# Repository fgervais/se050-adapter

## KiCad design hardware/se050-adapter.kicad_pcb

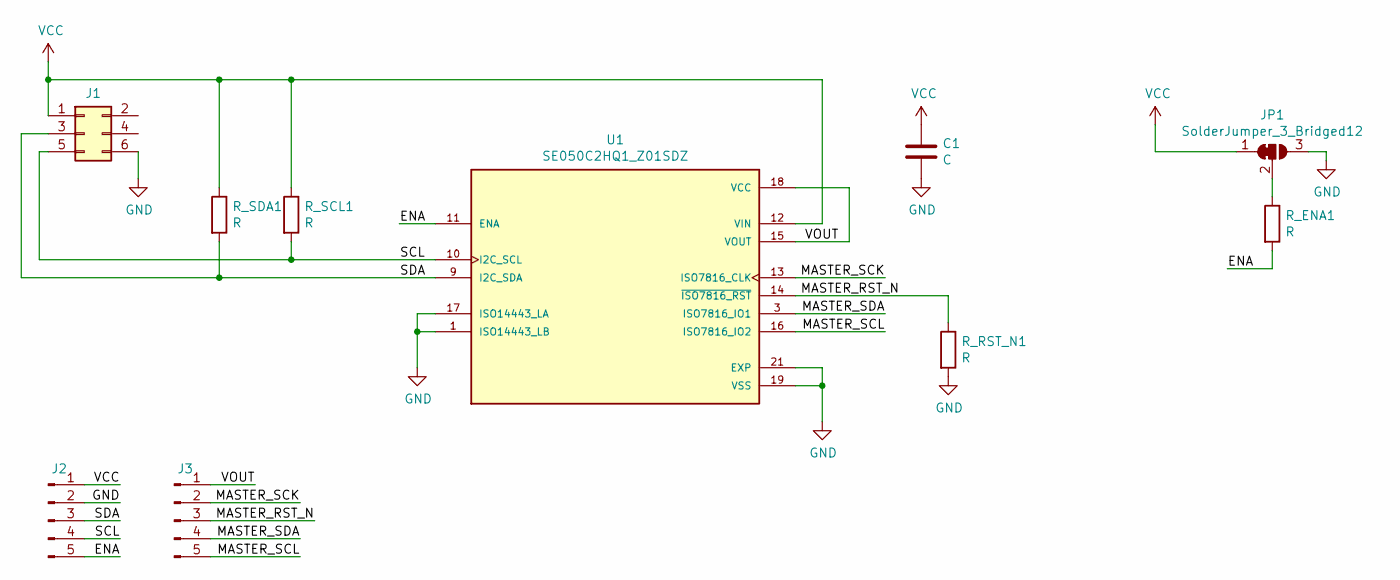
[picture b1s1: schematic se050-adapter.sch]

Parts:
C1: C; R_0603_1608Metric
J1: Conn_02x03_Odd_Even; PinSocket_2x03_P2.54mm_Vertical
J2, J3: Conn_01x05_Male; PinHeader_1x05_P2.54mm_Vertical
JP1: SolderJumper_3_Bridged12; SolderJumper-3_P1.3mm_Bridged12_RoundedPad1.0x1.5mm
R_ENA1: R; R_0603_1608Metric
R_RST_N1: R; R_0603_1608Metric
R_SCL1: R; R_0603_1608Metric
R_SDA1: R; R_0603_1608Metric
U1: SE050C2HQ1_Z01SDZ; QFN40P300X300X33-21N; PARTREV 1.3

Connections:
/ENA: J2.5, R_ENA1.2, U1.11 (ENA)
/MASTER_RST_N: J3.3, R_RST_N1.1, U1.14 (~ISO7816_RST)
/MASTER_SCK: J3.2, U1.13 (ISO7816_CLK)
/MASTER_SCL: J3.5, U1.16 (ISO7816_IO2)
/MASTER_SDA: J3.4, U1.3 (ISO7816_IO1)
/SCL: J1.5, J2.4, R_SCL1.2, U1.10 (I2C_SCL)
/SDA: J1.3, J2.3, R_SDA1.2, U1.9 (I2C_SDA)
/VOUT: J3.1, U1.15 (VOUT), U1.18 (VCC)
GND: C1.2, J1.6, J2.2, JP1.3 (B), R_RST_N1.2, U1.1 (ISO14443_LB), U1.17 (ISO14443_LA), U1.19 (VSS), U1.21 (EXP)
unnamed: JP1.2 (C), R_ENA1.1
VCC: C1.1, J1.1, J2.1, JP1.1 (A), R_SCL1.1, R_SDA1.1, U1.12 (VIN)

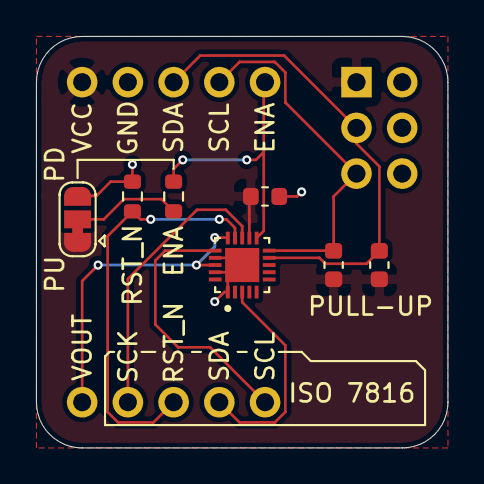
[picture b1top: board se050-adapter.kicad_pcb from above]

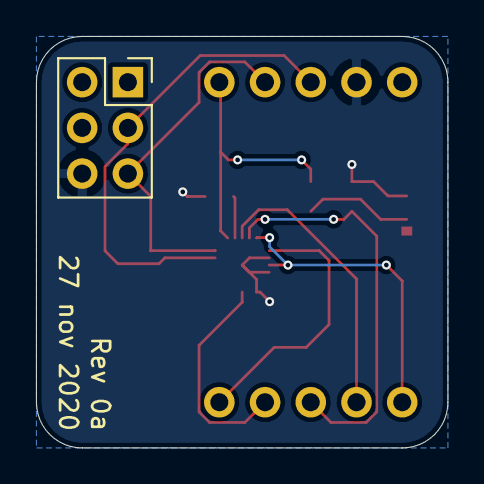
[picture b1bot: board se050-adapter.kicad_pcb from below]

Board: 2 copper layers, 22.9 x 22.9 mm, 10 parts (3 on the bottom side), 11 nets.

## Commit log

2020-12-03 hardware: rev 0a
